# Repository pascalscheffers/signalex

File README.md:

# signalex
Code and PCB for driving Signalex 7 Segment Displays.

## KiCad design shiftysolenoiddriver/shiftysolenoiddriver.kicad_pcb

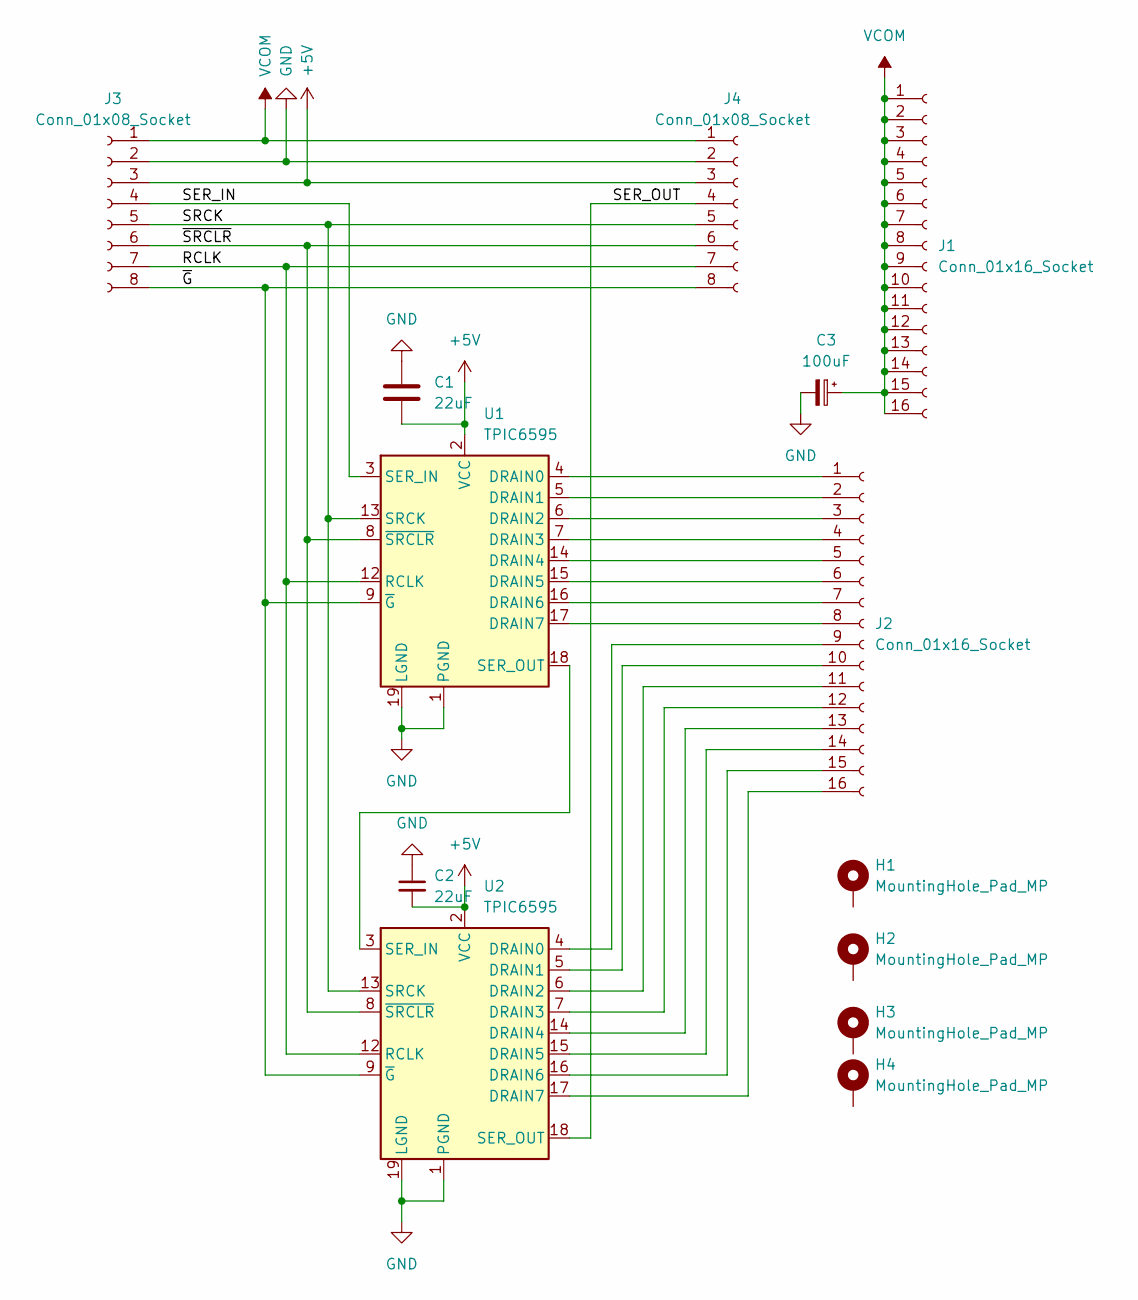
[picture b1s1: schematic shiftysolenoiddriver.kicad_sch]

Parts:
C1, C2: 22uF; C_0805_2012Metric
C3: 100uF; CP_Radial_D8.0mm_P3.50mm
H1, H2, H3, H4: MountingHole_Pad_MP; MountingHole_2.2mm_M2_ISO14580_Pad
J1, J2: Conn_01x16_Socket; PinHeader_1x16_P2.54mm_Vertical
J3, J4: Conn_01x08_Socket; PinHeader_1x08_P2.54mm_Vertical
U1, U2: TPIC6595; SOIC-20W_7.5x12.8mm_P1.27mm

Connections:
+5V: C1.2, C2.2, J3.3, J4.3, U1.2 (VCC), U2.2 (VCC)
/RCLK: J3.7, J4.7, U1.12 (RCLK), U2.12 (RCLK)
/SER_IN: J3.4, U1.3 (SER_IN)
/SER_OUT: J4.4, U2.18 (SER_OUT)
/SRCK: J3.5, J4.5, U1.13 (SRCK), U2.13 (SRCK)
/~G: J3.8, J4.8, U1.9 (~G), U2.9 (~G)
/~SRCLR: J3.6, J4.6, U1.8 (~SRCLR), U2.8 (~SRCLR)
GND: C1.1, C2.1, C3.2, J3.2, J4.2, U1.1 (PGND), U1.10 (PGND), U1.11 (PGND), U1.19 (LGND), U1.20 (PGND), U2.1 (PGND), U2.10 (PGND), U2.11 (PGND), U2.19 (LGND), U2.20 (PGND)
unnamed: J2.1, U1.4 (DRAIN0)
unnamed: J2.2, U1.5 (DRAIN1)
unnamed: J2.3, U1.6 (DRAIN2)
unnamed: J2.4, U1.7 (DRAIN3)
unnamed: J2.5, U1.14 (DRAIN4)
unnamed: J2.6, U1.15 (DRAIN5)
unnamed: J2.7, U1.16 (DRAIN6)
unnamed: J2.8, U1.17 (DRAIN7)
unnamed: J2.9, U2.4 (DRAIN0)
unnamed: J2.10, U2.5 (DRAIN1)
unnamed: J2.11, U2.6 (DRAIN2)
unnamed: J2.12, U2.7 (DRAIN3)
unnamed: J2.13, U2.14 (DRAIN4)
unnamed: J2.14, U2.15 (DRAIN5)
unnamed: J2.15, U2.16 (DRAIN6)
unnamed: J2.16, U2.17 (DRAIN7)
unnamed: U1.18 (SER_OUT), U2.3 (SER_IN)
VCOM: C3.1, J1.1, J1.2, J1.3, J1.4, J1.5, J1.6, J1.7, J1.8, J1.9, J1.10, J1.11, J1.12, J1.13, J1.14, J1.15, J1.16, J3.1, J4.1

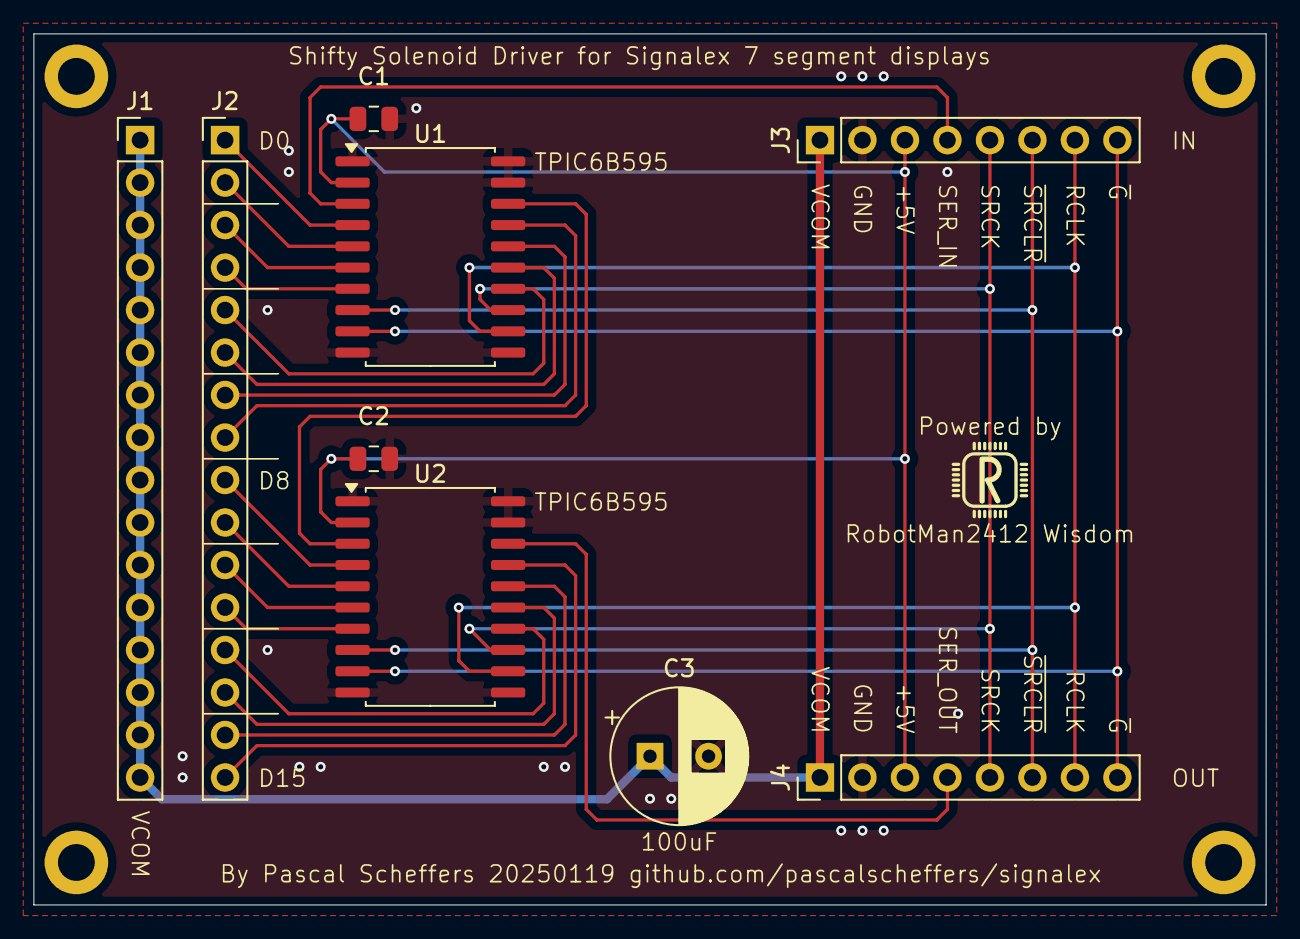
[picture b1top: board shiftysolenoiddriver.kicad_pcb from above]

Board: 2 copper layers, 73.7 x 52.1 mm, 13 parts (0 on the bottom side), 26 nets.

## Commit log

2025-01-19 Commit first version of KiCad design
